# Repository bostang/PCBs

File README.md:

# PCBs
My repository for documenting all PCB Projects I have done

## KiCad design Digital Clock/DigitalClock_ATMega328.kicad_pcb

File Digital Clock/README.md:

# Digital Clock

# Skematik

# Tampilan

## Tampak Atas

## Tampak Bawah

## Bird-view

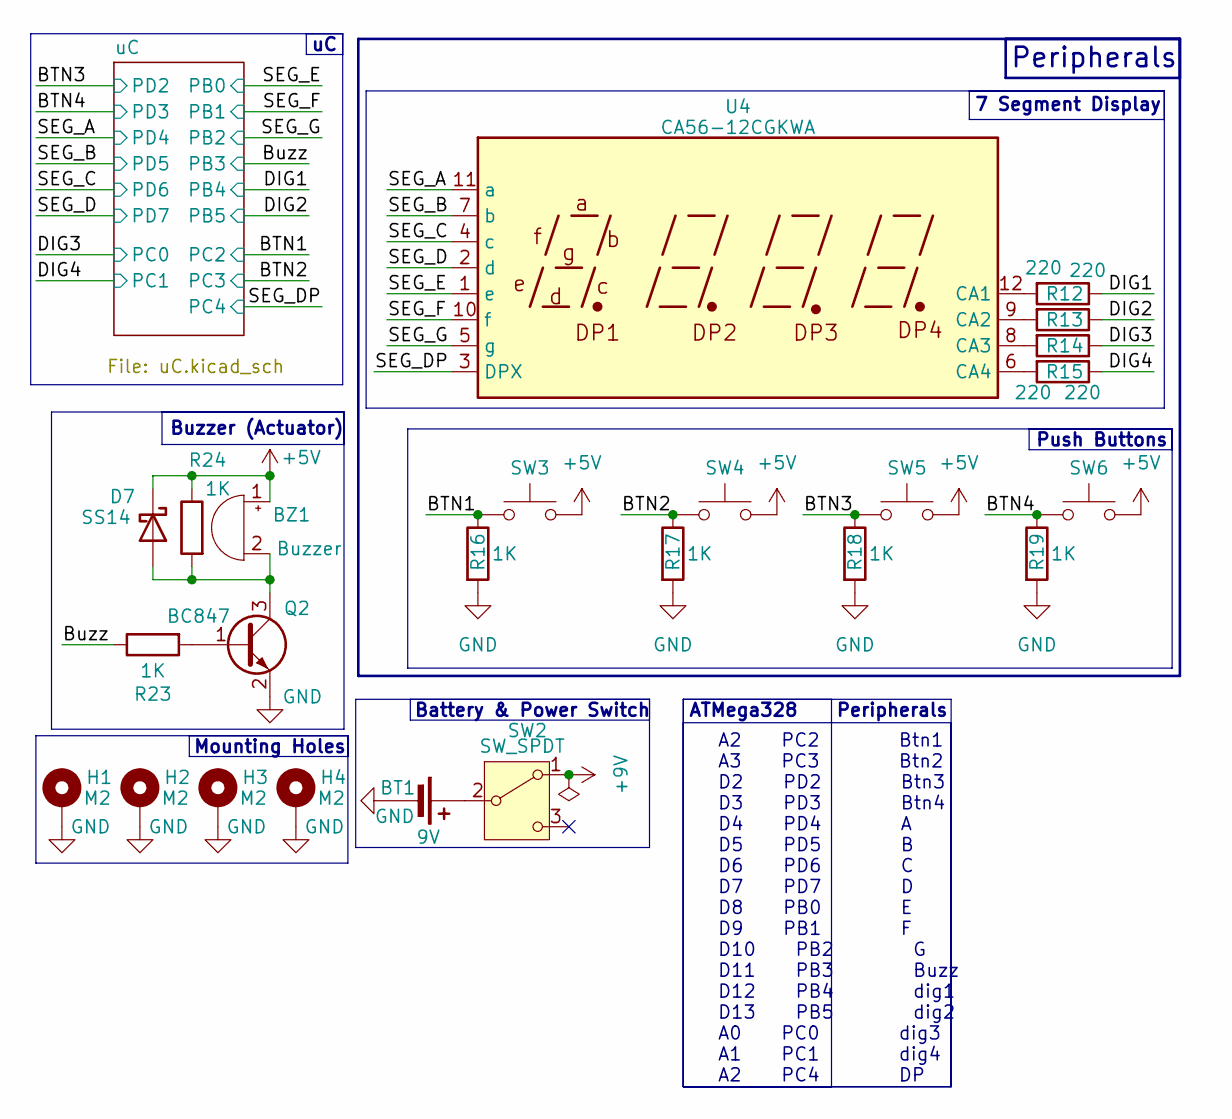
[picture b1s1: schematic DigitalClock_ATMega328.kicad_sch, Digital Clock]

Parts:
BT1: 9V; BatteryHolder_Eagle_12BH611-GR
BZ1: Buzzer; MagneticBuzzer_Kobitone_254-EMB84Q-RO
D7: SS14; D_SMA
H1, H2, H3, H4: M2; MountingHole_2.2mm_M2_Pad_Via
Q2: BC847; SOT-23
R12, R13, R14, R15: 220; R_0805_2012Metric
R16, R17, R18, R19, R23, R24: 1K; R_0805_2012Metric
SW2: SW_SPDT; SW_Slide_SPDT_Angled_CK_OS102011MA1Q
SW3, SW4, SW5, SW6: SW_Push; SW_SPST_PTS645
U4: CA56-12CGKWA

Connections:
+5V: BZ1.1 (+), D7.1 (K), R24.1, SW3.2, SW4.2, SW5.2, SW6.2; also elsewhere on the board
+9V: SW2.1 (A); also elsewhere on the board
/BTN1: R16.1, SW3.1; also elsewhere on the board
/BTN2: R17.1, SW4.1; also elsewhere on the board
/BTN3: R18.1, SW5.1; also elsewhere on the board
/BTN4: R19.1, SW6.1; also elsewhere on the board
/Buzz: R23.1; also elsewhere on the board
/DIG1: R12.1; also elsewhere on the board
/DIG2: R13.1; also elsewhere on the board
/DIG3: R14.1; also elsewhere on the board
/DIG4: R15.1; also elsewhere on the board
/SEG_A: U4.11 (a); also elsewhere on the board
/SEG_B: U4.7 (b); also elsewhere on the board
/SEG_C: U4.4 (c); also elsewhere on the board
/SEG_D: U4.2 (d); also elsewhere on the board
/SEG_DP: U4.3 (DPX); also elsewhere on the board
/SEG_E: U4.1 (e); also elsewhere on the board
/SEG_F: U4.10 (f); also elsewhere on the board
/SEG_G: U4.5 (g); also elsewhere on the board
GND: BT1.2 (-), H1.1, H2.1, H3.1, H4.1, Q2.2 (E), R16.2, R17.2, R18.2, R19.2; also elsewhere on the board
unnamed: BT1.1 (+), SW2.2 (B)
unnamed: BZ1.2 (-), D7.2 (A), Q2.3 (C), R24.2
unnamed: Q2.1 (B), R23.2
unnamed: R12.2, U4.12 (CA1)
unnamed: R13.2, U4.9 (CA2)
unnamed: R14.2, U4.8 (CA3)
unnamed: R15.2, U4.6 (CA4)

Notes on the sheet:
7 Segment Display
Push Buttons
A2 PC2 Btn1 A3 PC3 Btn2 D2 PD2 Btn3 D3 PD3 Btn4 D4 PD4 A D5 PD5 B D6 PD6 C D7 PD7 D D8 PB0 E D9 PB1 F D10 PB2 G D11 PB3 Buzz D12 PB4 dig1 D13 PB5 dig2 A0 PC0 dig3 A1 PC1 dig4 A2 PC4 DP
Buzzer (Actuator)
Mounting Holes
Battery & Power Switch
ATMega328 Peripherals
Peripherals

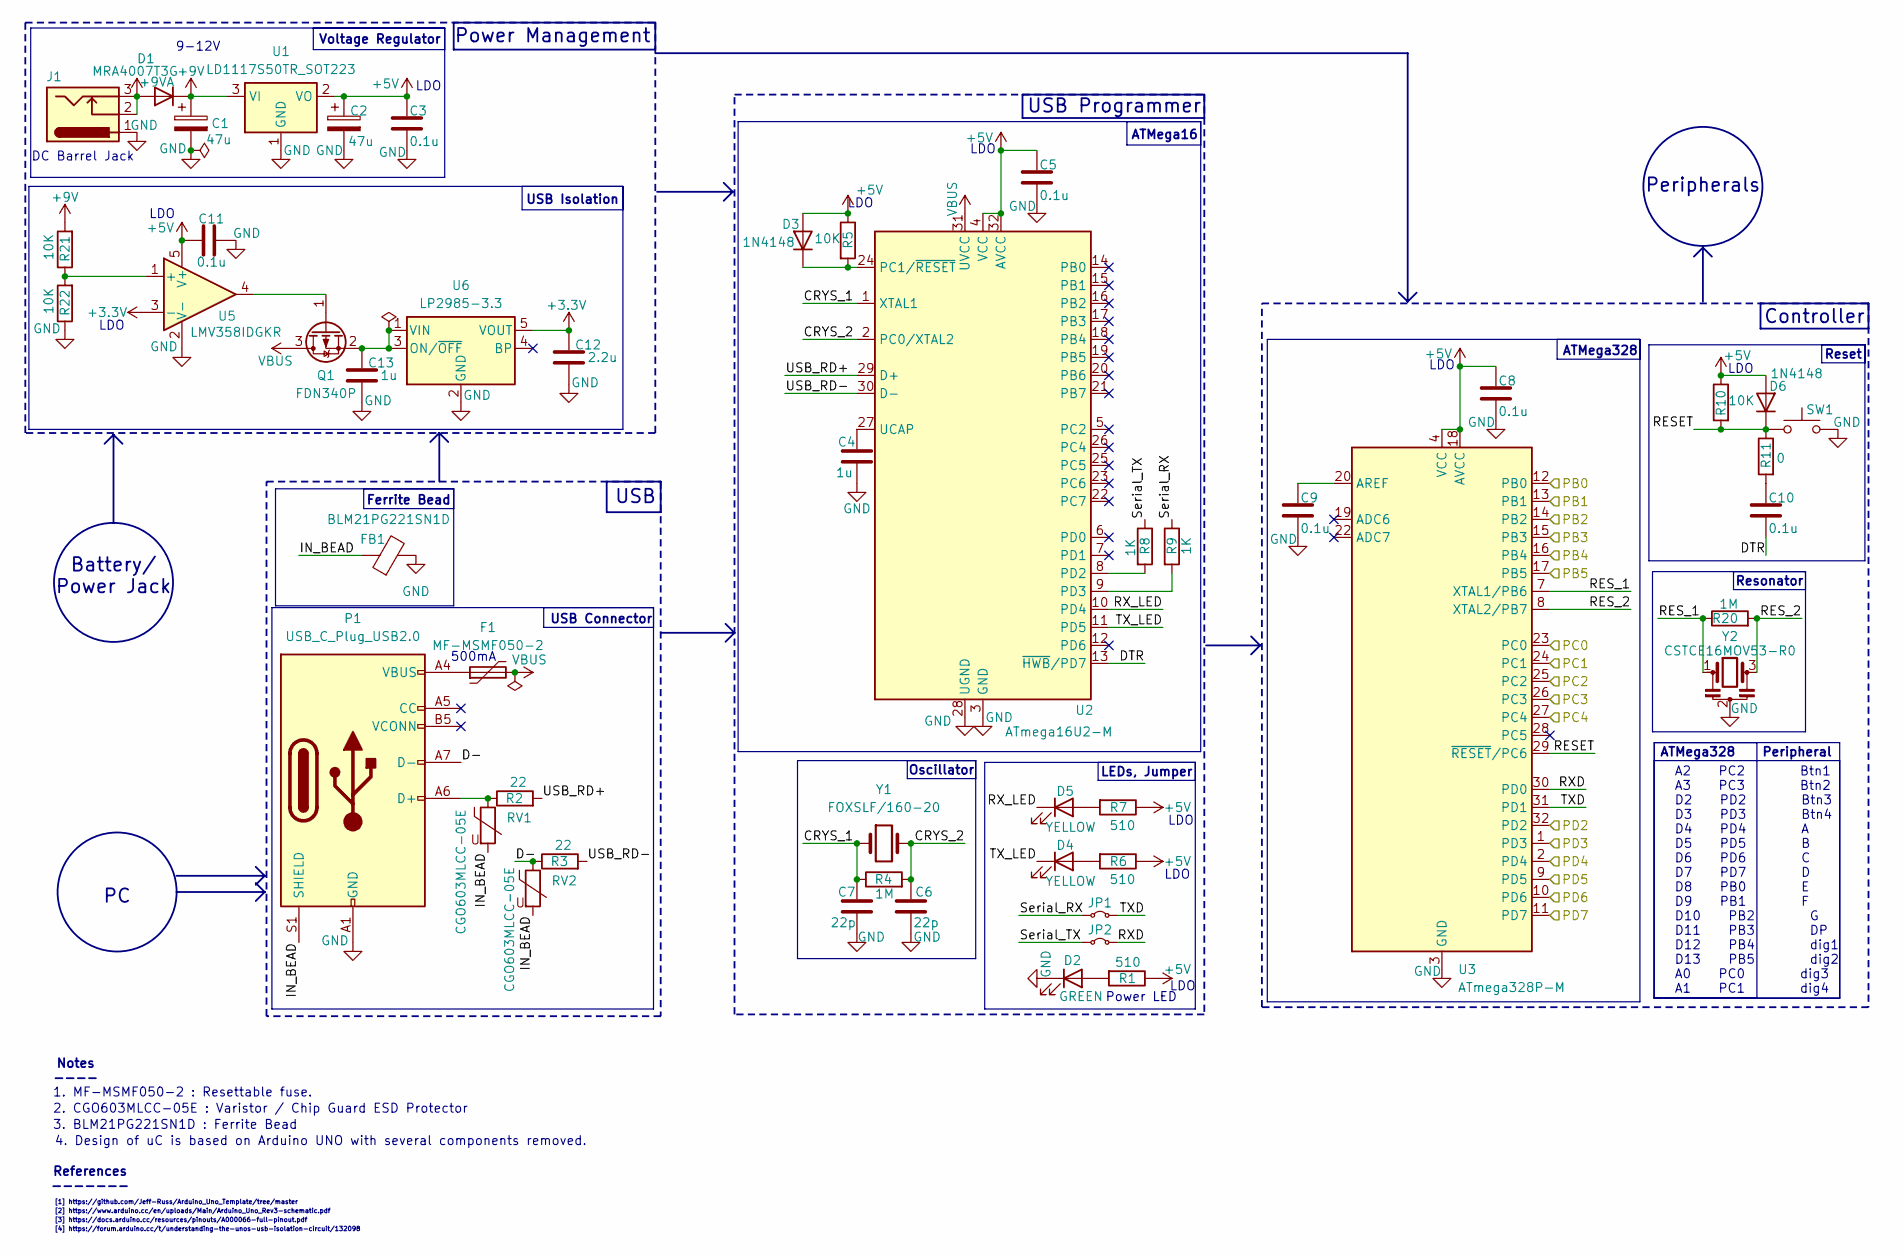
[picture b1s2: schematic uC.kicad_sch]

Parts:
C1, C2: 47u; C_Elec_3x5.4
C3: 0.1u; C_1206_3216Metric
C4: 1u; C_0201_0603Metric
C5, C8, C9, C11: 0.1u; C_0201_0603Metric
C6, C7: 22p; C_0201_0603Metric
C10: 0.1u; C_0805_2012Metric
C12: 2.2u; C_0402_1005Metric
C13: 1u; C_0402_1005Metric
D1: MRA4007T3G; D_SMA
D2: GREEN; LED_0805_2012Metric
D3, D6: 1N4148; D_SOD-323F
D4, D5: YELLOW; LED_0805_2012Metric
F1: MF-MSMF050-2; R_1812_4532Metric
FB1: BLM21PG221SN1D; R_0603_1608Metric
J1: Barrel_Jack_Switch_Pin3Ring; BarrelJack_Horizontal
JP1, JP2: Jumper_2_Small_Bridged; SolderJumper-2_P1.3mm_Bridged_Pad1.0x1.5mm
P1: USB_C_Plug_USB2.0; USB_C_Receptacle_GCT_USB4105-xx-A_16P_TopMnt_Horizontal
Q1: FDN340P; SOT-23
R1, R6, R7: 510; R_0805_2012Metric
R2, R3: 22; R_0603_1608Metric
R4: 1M; R_0805_2012Metric
R5, R21, R22: 10K; R_0201_0603Metric
R8, R9: 1K; R_0201_0603Metric
R10: 10K; R_0805_2012Metric
R11: 0; R_0805_2012Metric
R20: 1M; R_0201_0603Metric
RV1, RV2: CGO603MLCC-05E; R_0603_1608Metric
SW1: SW_Push; SW_SPST_B3U-1000P
U1: LD1117S50TR_SOT223; SOT-223-3_TabPin2
U2: ATmega16U2-M; QFN-32-1EP_5x5mm_P0.5mm_EP3.3x3.3mm
U3: ATmega328P-M; QFN-32-1EP_5x5mm_P0.5mm_EP3.3x3.3mm
U5: LMV358IDGKR; VSSOP-8_2.3x2mm_P0.5mm
U6: LP2985-3.3; SOT-23-5
Y1: FOXSLF/160-20; Crystal_HC49-4H_Vertical
Y2: CSTCE16MOV53-R0; Resonator_SMD_Murata_CSTxExxV-3Pin_3.0x1.1mm

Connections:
+3.3V: C12.1, U5.3 (-), U6.5 (VOUT)
+5V: C2.1, C3.1, C5.1, C8.1, C11.1, D3.2 (A), D6.2 (A), R1.1, R5.1, R6.1, R7.1, R10.1, U1.2 (VO), U2.4 (VCC), U2.32 (AVCC), U3.4 (VCC), U3.6 (VCC), U3.18 (AVCC), U5.5 (V+); also elsewhere on the board
+9V: C1.1, D1.1 (K), R21.2, U1.3 (VI); also elsewhere on the board
+9VA: D1.2 (A), J1.2, J1.3
/BTN1: U3.25 (PC2); also elsewhere on the board
/BTN2: U3.26 (PC3); also elsewhere on the board
/BTN3: U3.32 (PD2); also elsewhere on the board
/BTN4: U3.1 (PD3); also elsewhere on the board
/Buzz: U3.15 (PB3); also elsewhere on the board
/DIG1: U3.16 (PB4); also elsewhere on the board
/DIG2: U3.17 (PB5); also elsewhere on the board
/DIG3: U3.23 (PC0); also elsewhere on the board
/DIG4: U3.24 (PC1); also elsewhere on the board
/SEG_A: U3.2 (PD4); also elsewhere on the board
/SEG_B: U3.9 (PD5); also elsewhere on the board
/SEG_C: U3.10 (PD6); also elsewhere on the board
/SEG_D: U3.11 (PD7); also elsewhere on the board
/SEG_DP: U3.27 (PC4); also elsewhere on the board
/SEG_E: U3.12 (PB0); also elsewhere on the board
/SEG_F: U3.13 (PB1); also elsewhere on the board
/SEG_G: U3.14 (PB2); also elsewhere on the board
/uC/CRYS_1: C7.1, R4.1, U2.1 (XTAL1), Y1.1
/uC/CRYS_2: C6.1, R4.2, U2.2 (PC0/XTAL2), Y1.2
/uC/D-: P1.A7 (D-), R3.1, RV2.1
/uC/DTR: C10.2, U2.13 (~HWB/PD7)
/uC/IN_BEAD: FB1.1, P1.S1 (SHIELD), RV1.2, RV2.2
/uC/RESET: D6.1 (K), R10.2, R11.1, SW1.1, U3.29 (~RESET/PC6)
/uC/RES_1: R20.1, U3.7 (XTAL1/PB6), Y2.1
/uC/RES_2: R20.2, U3.8 (XTAL2/PB7), Y2.3
/uC/RXD: JP2.2 (B), U3.30 (PD0)
/uC/RX_LED: D5.1 (K), U2.10 (PD4)
/uC/Serial_RX: JP1.1 (A), R9.1
/uC/Serial_TX: JP2.1 (A), R8.1
/uC/TXD: JP1.2 (B), U3.31 (PD1)
/uC/TX_LED: D4.1 (K), U2.11 (PD5)
/uC/USB_RD+: R2.2, U2.29 (D+)
/uC/USB_RD-: R3.2, U2.30 (D-)
GND: C1.2, C2.2, C3.2, C4.2, C5.2, C6.2, C7.2, C8.2, C9.2, C11.2, C12.2, C13.2, D2.1 (K), FB1.2, J1.1, P1.A1 (GND), P1.A12 (GND), P1.B1 (GND), P1.B12 (GND), R22.1, SW1.2, U1.1 (GND), U2.3 (GND), U2.28 (UGND), U2.33 (GND), U3.3 (GND), U3.5 (GND), U3.21 (GND), U3.33 (GND), U5.2 (V-), U6.2 (GND), Y2.2; also elsewhere on the board
unnamed: C10.1, R11.2
unnamed: D2.2 (A), R1.2
unnamed: D3.1 (K), R5.2, U2.24 (PC1/~RESET)
unnamed: D4.2 (A), R6.2
unnamed: D5.2 (A), R7.2
unnamed: F1.1, P1.A4 (VBUS), P1.A9 (VBUS), P1.B4 (VBUS), P1.B9 (VBUS)
unnamed: P1.A6 (D+), R2.1, RV1.1
unnamed: Q1.1 (G), U5.4
unnamed: C13.1, Q1.2 (S), U6.1 (VIN), U6.3 (ON/~OFF)
unnamed: R8.2, U2.8 (PD2)
unnamed: R9.2, U2.9 (PD3)
unnamed: C4.1, U2.27 (UCAP)
unnamed: C9.1, U3.20 (AREF)
unnamed: R21.1, R22.2, U5.1 (+)
VBUS: F1.2, Q1.3 (D), U2.31 (UVCC)

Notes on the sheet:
LDO
Power Management
References -------
Resonator
Oscillator
[2] https://www.arduino.cc/en/uploads/Main/Arduino_Uno_Rev3-schematic.pdf
1. MF-MSMF050-2 : Resettable fuse.
ATMega328 Peripheral
[4] https://forum.arduino.cc/t/understanding-the-unos-usb-isolation-circuit/132098
ATMega16
ATMega328
Controller
DC Barrel Jack
Notes ----
4. Design of uC is based on Arduino UNO with several components removed.
[3] https://docs.arduino.cc/resources/pinouts/A000066-full-pinout.pdf
3. BLM21PG221SN1D : Ferrite Bead
[1] https://github.com/Jeff-Russ/Arduino_Uno_Template/tree/master
500mA
USB
USB Connector
USB Programmer
A2 PC2 Btn1 A3 PC3 Btn2 D2 PD2 Btn3 D3 PD3 Btn4 D4 PD4 A D5 PD5 B D6 PD6 C D7 PD7 D D8 PB0 E D9 PB1 F D10 PB2 G D11 PB3 DP D12 PB4 dig1 D13 PB5 dig2 A0 PC0 dig3 A1 PC1 dig4
2. CGO603MLCC-05E : Varistor / Chip Guard ESD Protector
Battery/ Power Jack
LEDs, Jumper
Ferrite Bead
USB Isolation
Voltage Regulator
Power LED
Peripherals
Reset
9-12V

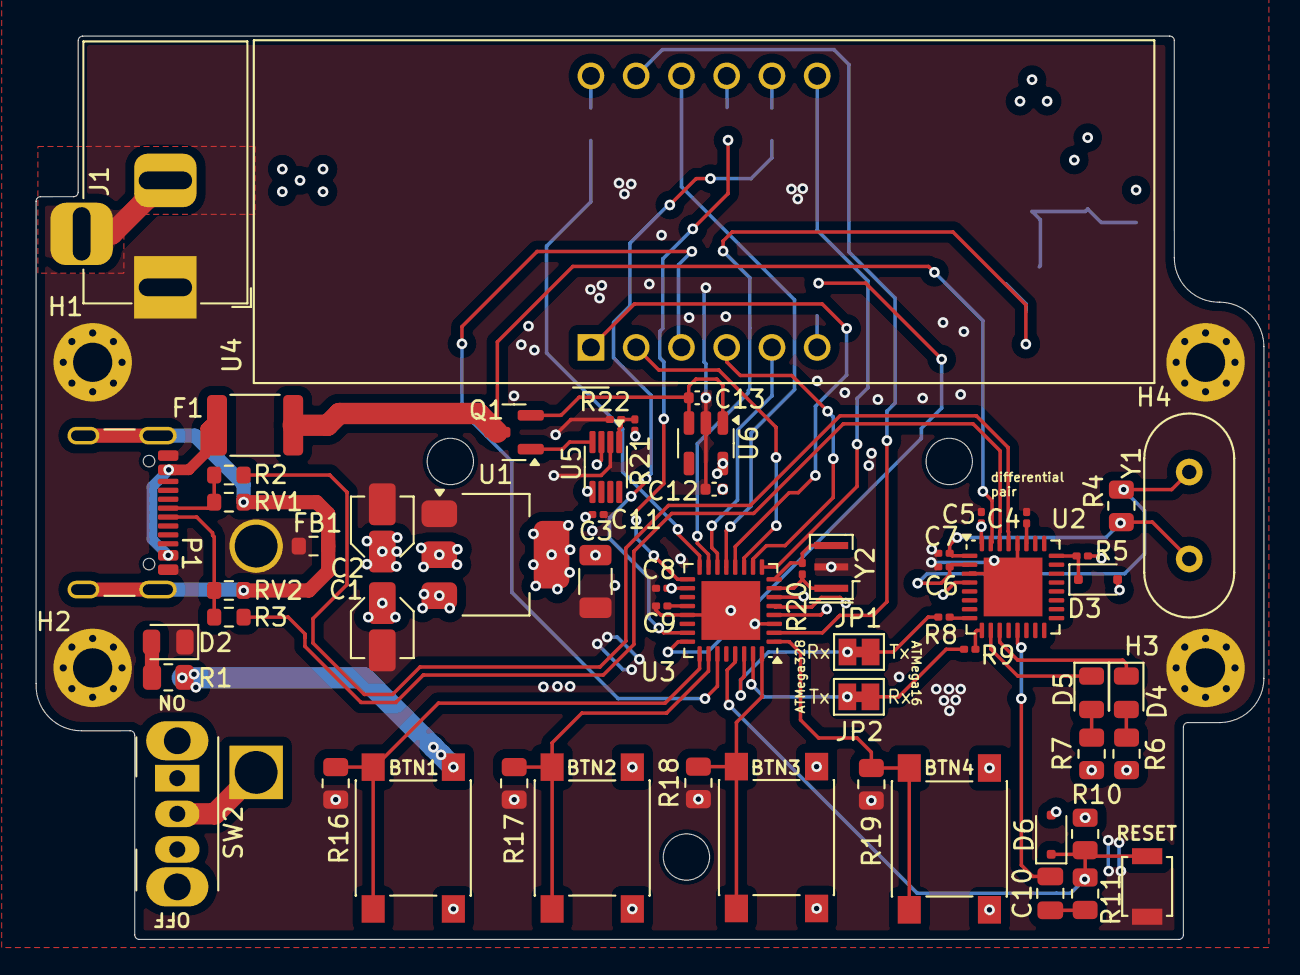
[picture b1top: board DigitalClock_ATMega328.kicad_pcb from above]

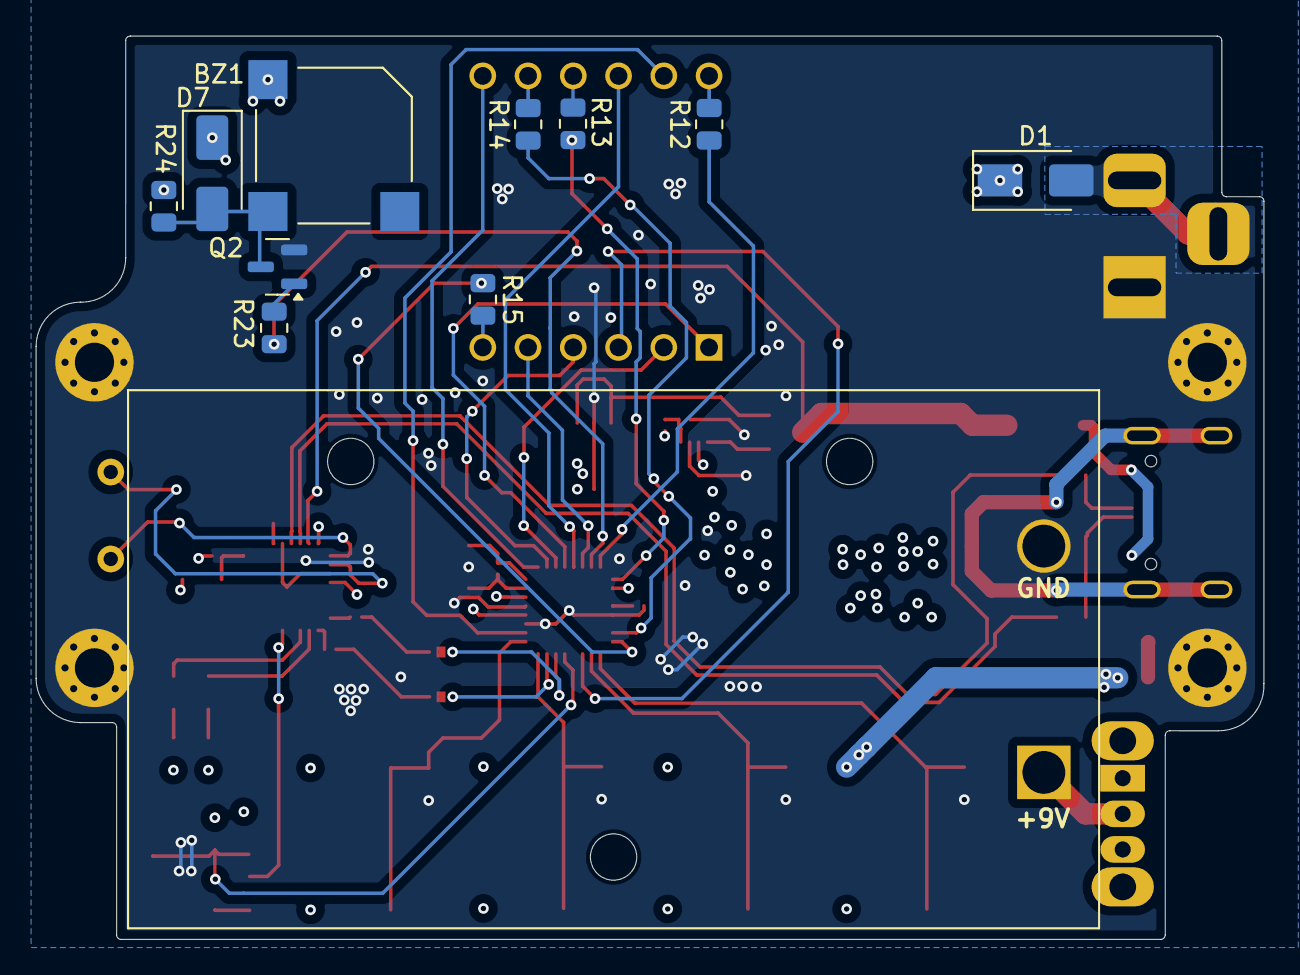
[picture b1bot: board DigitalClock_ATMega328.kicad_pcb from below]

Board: 4 copper layers, 68.9 x 50.7 mm, 74 parts (11 on the bottom side), 60 nets.

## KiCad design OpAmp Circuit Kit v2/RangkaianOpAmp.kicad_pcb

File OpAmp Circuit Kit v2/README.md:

# Op Amp Circuits Kit

Kit Praktikum EL2101 Praktikum Rangkaian Elektrik Modul 3. (v2)

# Skematik

# Tampilan

## Tampak Atas

## Tampak Bawah

## Bird-view

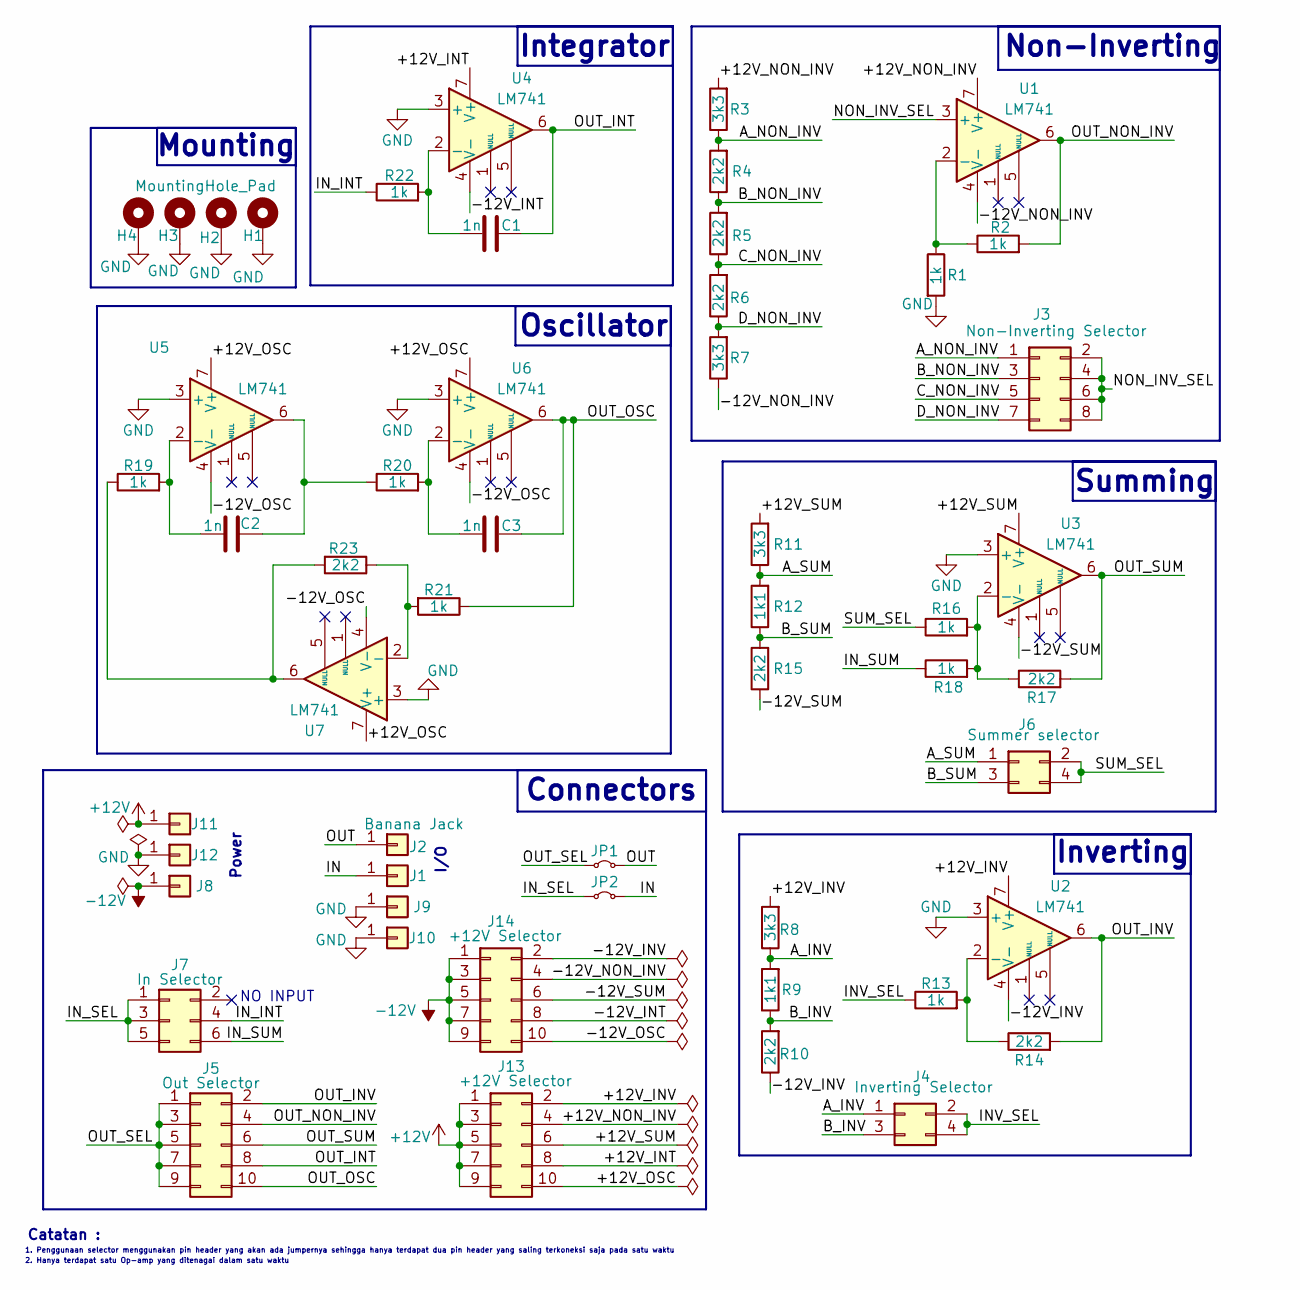
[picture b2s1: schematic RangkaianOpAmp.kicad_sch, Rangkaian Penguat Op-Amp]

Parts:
C1, C2, C3: 1n; C_0805_2012Metric
H1, H2, H3, H4: MountingHole_Pad; MountingHole_3.2mm_M3_Pad_Via
J1, J2, J8, J9, J10, J11, J12: Banana Jack; Banana_Jack_1Pin
J3: Non-Inverting Selector; PinHeader_2x04_P2.54mm_Vertical
J4: Inverting Selector; PinHeader_2x02_P2.54mm_Vertical
J5: Out Selector; PinHeader_2x05_P2.54mm_Vertical
J6: Summer selector; PinHeader_2x02_P2.54mm_Vertical
J7: In Selector; PinHeader_2x03_P2.54mm_Vertical
J13, J14: +12V Selector; PinHeader_2x05_P2.54mm_Vertical
JP1, JP2: Jumper_2_Small_Bridged; SolderJumper-2_P1.3mm_Bridged2Bar_RoundedPad1.0x1.5mm
R1, R2, R13, R16, R18, R19, R20, R21, R22: 1k; R_0805_2012Metric
R3, R7, R8, R11: 3k3; R_0805_2012Metric
R4, R5, R6, R10, R14, R15, R17, R23: 2k2; R_0805_2012Metric
R9, R12: 1k1; R_0805_2012Metric
U1, U2, U3, U4, U5, U6, U7: LM741; SOIC-8_3.9x4.9mm_P1.27mm

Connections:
+12V: J11.1, J13.1, J13.3, J13.5, J13.7, J13.9
-12V: J8.1, J14.1, J14.3, J14.5, J14.7, J14.9
/+12V_INT: J13.8, U4.7 (V+)
/+12V_INV: J13.2, R8.2, U2.7 (V+)
/+12V_NON_INV: J13.4, R3.2, U1.7 (V+)
/+12V_OSC: J13.10, U5.7 (V+), U6.7 (V+), U7.7 (V+)
/+12V_SUM: J13.6, R11.2, U3.7 (V+)
/-12V_INT: J14.8, U4.4 (V-)
/-12V_INV: J14.2, R10.1, U2.4 (V-)
/-12V_NON_INV: J14.4, R7.1, U1.4 (V-)
/-12V_OSC: J14.10, U5.4 (V-), U6.4 (V-), U7.4 (V-)
/-12V_SUM: J14.6, R15.1, U3.4 (V-)
/A_INV: J4.1, R8.1, R9.2
/A_NON_INV: J3.1, R3.1, R4.2
/A_SUM: J6.1, R11.1, R12.2
/B_INV: J4.3, R9.1, R10.2
/B_NON_INV: J3.3, R4.1, R5.2
/B_SUM: J6.3, R12.1, R15.2
/C_NON_INV: J3.5, R5.1, R6.2
/D_NON_INV: J3.7, R6.1, R7.2
/IN: J1.1, JP2.2 (B)
/INV_SEL: J4.2, J4.4, R13.1
/IN_INT: J7.4, R22.1
/IN_SEL: J7.1, J7.3, J7.5, JP2.1 (A)
/IN_SUM: J7.6, R18.1
/NON_INV_SEL: J3.2, J3.4, J3.6, J3.8, U1.3 (+)
/OUT: J2.1, JP1.2 (B)
/OUT_INT: C1.2, J5.8, U4.6
/OUT_INV: J5.2, R14.2, U2.6
/OUT_NON_INV: J5.4, R2.2, U1.6
/OUT_OSC: C3.2, J5.10, R21.1, U6.6
/OUT_SEL: J5.1, J5.3, J5.5, J5.7, J5.9, JP1.1 (A)
/OUT_SUM: J5.6, R17.2, U3.6
/SUM_SEL: J6.2, J6.4, R16.1
GND: H1.1, H2.1, H3.1, H4.1, J9.1, J10.1, J12.1, R1.2, U2.3 (+), U3.3 (+), U4.3 (+), U5.3 (+), U6.3 (+), U7.3 (+)
unnamed: C2.2, R20.1, U5.6
unnamed: R19.1, R23.2, U7.6
unnamed: R1.1, R2.1, U1.2 (-)
unnamed: R13.2, R14.1, U2.2 (-)
unnamed: R16.2, R17.1, R18.2, U3.2 (-)
unnamed: C1.1, R22.2, U4.2 (-)
unnamed: C2.1, R19.2, U5.2 (-)
unnamed: C3.1, R20.2, U6.2 (-)
unnamed: R21.2, R23.1, U7.2 (-)

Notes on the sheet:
Inverting
Summing
Connectors
Mounting
Catatan :
1. Penggunaan selector menggunakan pin header yang akan ada jumpernya sehingga hanya terdapat dua pin header yang saling terkoneksi saja pada satu waktu
2. Hanya terdapat satu Op-amp yang ditenagai dalam satu waktu
Power
Non-Inverting
NO INPUT
Integrator
Oscillator
I/O

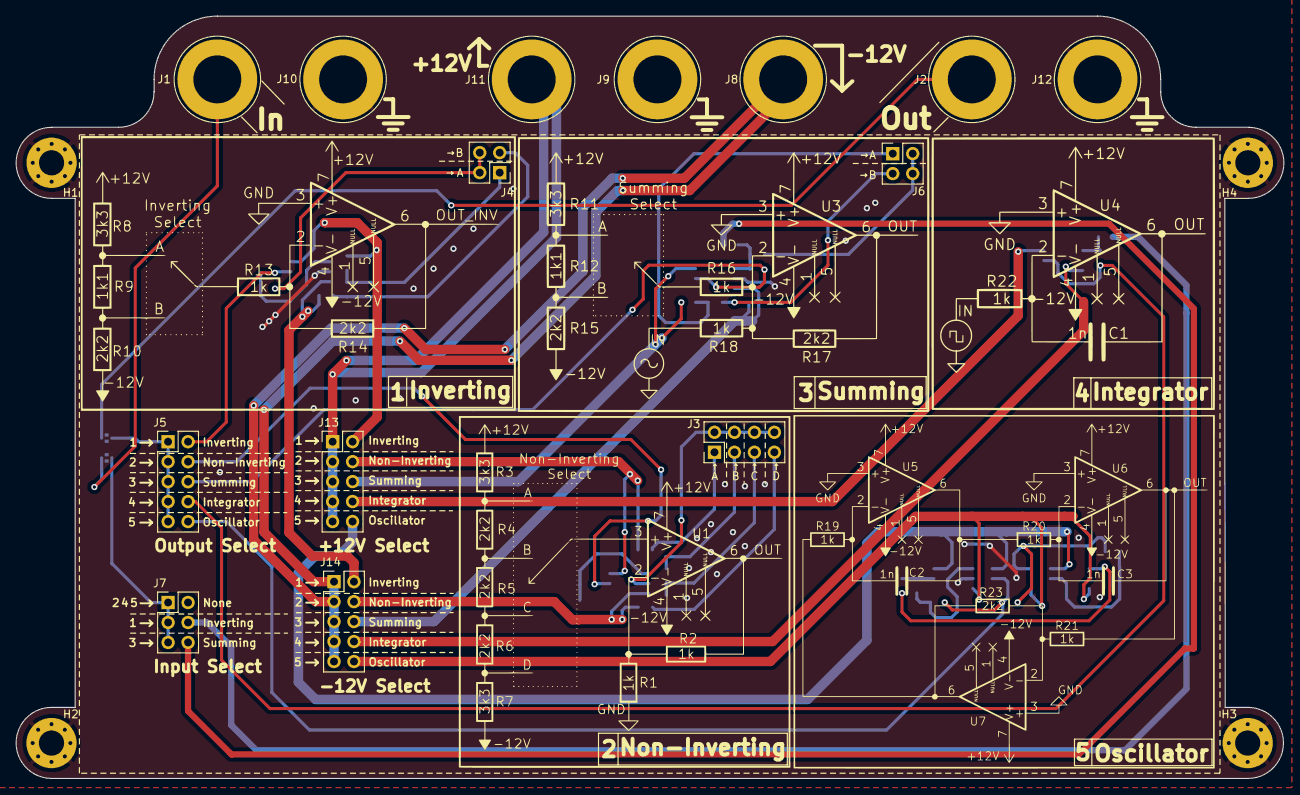
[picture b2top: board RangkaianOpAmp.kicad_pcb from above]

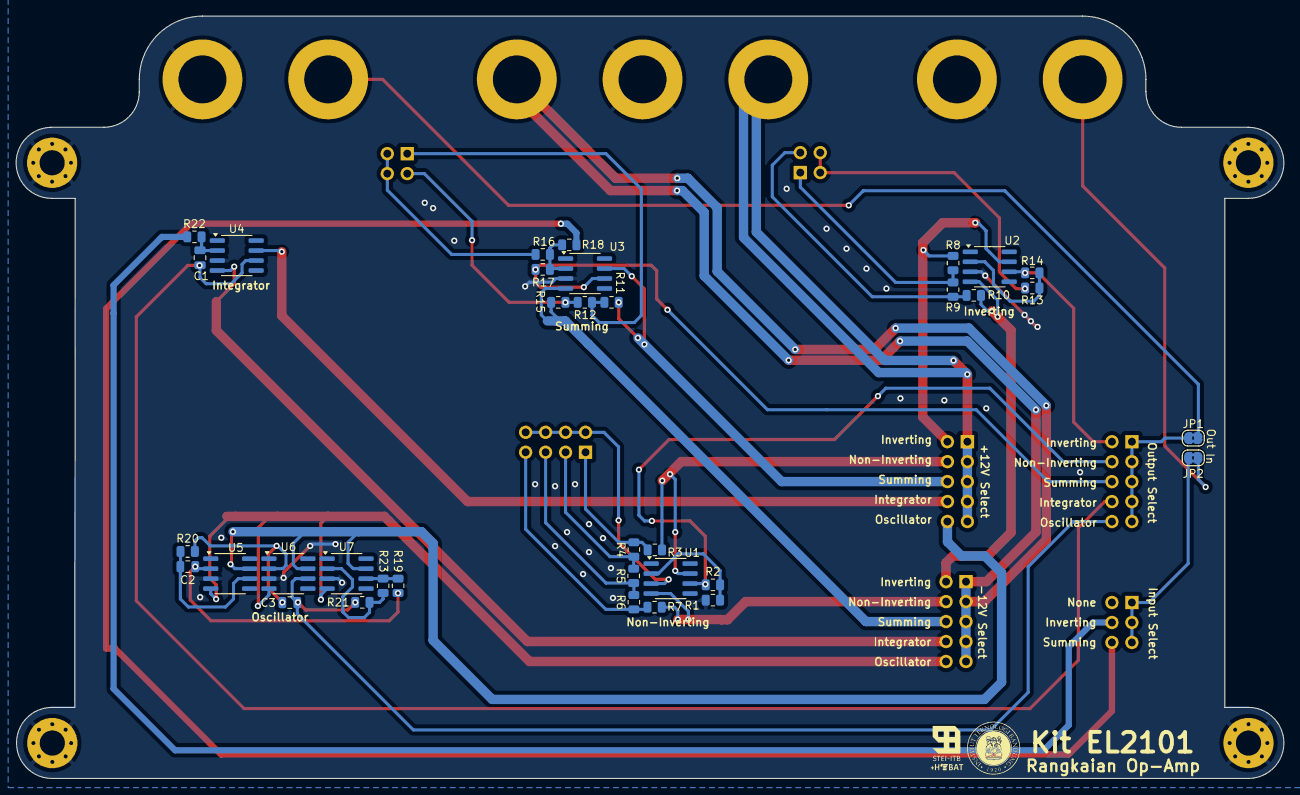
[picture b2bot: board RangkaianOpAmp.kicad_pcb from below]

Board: 2 copper layers, 161.3 x 97.0 mm, 53 parts (35 on the bottom side), 44 nets.

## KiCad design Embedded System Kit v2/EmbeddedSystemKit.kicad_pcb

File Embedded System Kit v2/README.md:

# Embedded System Kit (v2)

# Skematik

# Tampilan

## Tampak Atas

## Tampak Bawah

## Bird-view

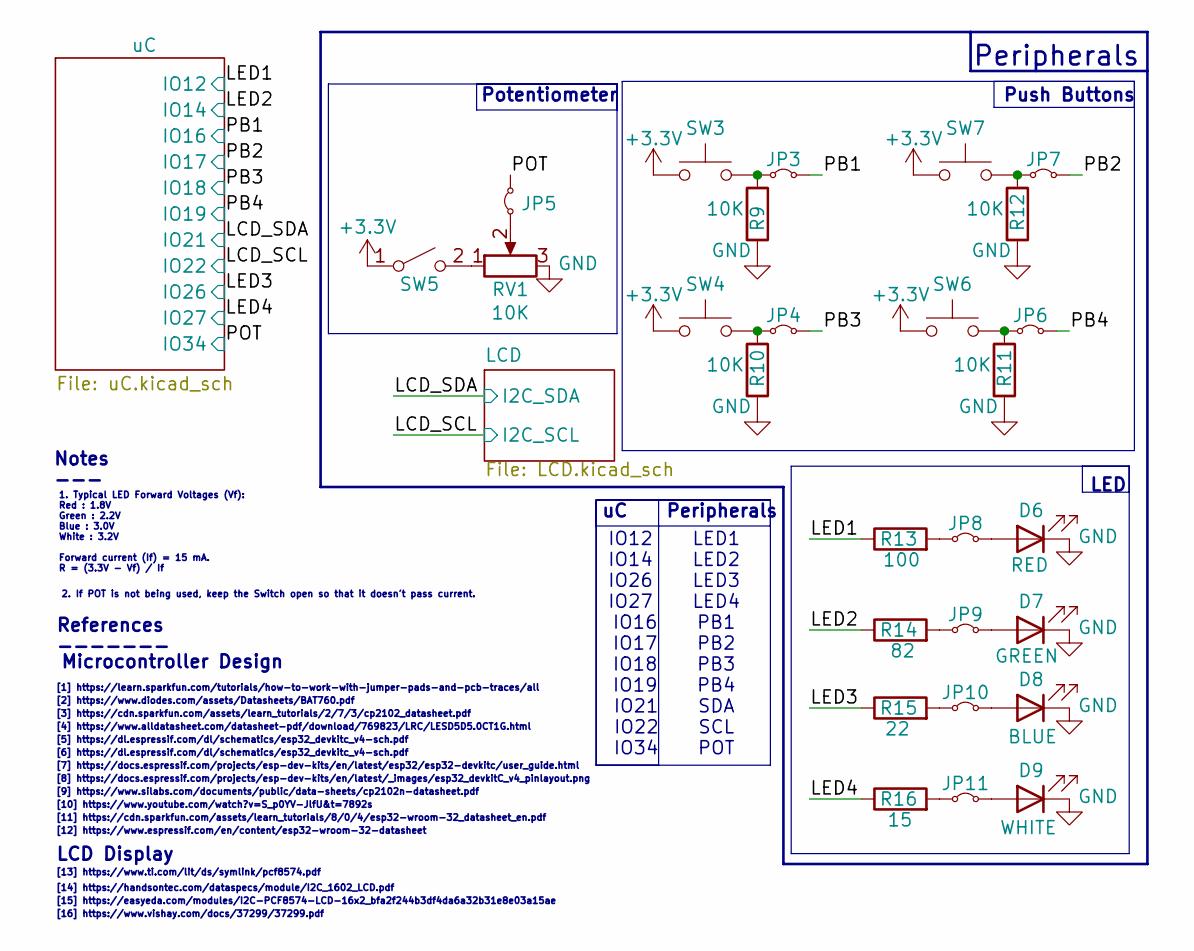
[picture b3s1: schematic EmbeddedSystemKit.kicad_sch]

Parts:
D6: RED; LED_0805_2012Metric
D7: GREEN; LED_0805_2012Metric
D8: BLUE; LED_0805_2012Metric
D9: WHITE; LED_0805_2012Metric
JP3, JP4, JP5, JP6, JP7, JP8, JP9, JP10, JP11: Jumper_2_Small_Bridged; R_0805_2012Metric
R9, R10, R11, R12: 10K; R_0805_2012Metric
R13: 100; R_0805_2012Metric
R14: 82; R_0805_2012Metric
R15: 22; R_0805_2012Metric
R16: 15; R_0805_2012Metric
RV1: 10K; Potentiometer_Bourns_PTV09A-1_Single_Vertical
SW3, SW4, SW6, SW7: SW_Push; SW_PUSH_6mm_H8mm
SW5: SW_SPST; SW_DIP_SPSTx01_Slide_6.7x4.1mm_W7.62mm_P2.54mm_LowProfile

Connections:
+3.3V: SW3.1, SW4.1, SW5.1 (A), SW6.1, SW7.1; also elsewhere on the board
/LED1: R13.1; also elsewhere on the board
/LED2: R14.1; also elsewhere on the board
/LED3: R15.1; also elsewhere on the board
/LED4: R16.1; also elsewhere on the board
/PB1: JP3.2 (B); also elsewhere on the board
/PB2: JP7.2 (B); also elsewhere on the board
/PB3: JP4.2 (B); also elsewhere on the board
/PB4: JP6.2 (B); also elsewhere on the board
/POT: JP5.2 (B); also elsewhere on the board
GND: D6.1 (K), D7.1 (K), D8.1 (K), D9.1 (K), R9.2, R10.2, R11.2, R12.2, RV1.3; also elsewhere on the board
unnamed: D6.2 (A), JP8.2 (B)
unnamed: D7.2 (A), JP9.2 (B)
unnamed: D8.2 (A), JP10.2 (B)
unnamed: D9.2 (A), JP11.2 (B)
unnamed: JP3.1 (A), R9.1, SW3.2
unnamed: JP4.1 (A), R10.1, SW4.2
unnamed: JP5.1 (A), RV1.2
unnamed: JP6.1 (A), R11.1, SW6.2
unnamed: JP7.1 (A), R12.1, SW7.2
unnamed: JP8.1 (A), R13.2
unnamed: JP9.1 (A), R14.2
unnamed: JP10.1 (A), R15.2
unnamed: JP11.1 (A), R16.2
unnamed: RV1.1, SW5.2 (B)

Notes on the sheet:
[5] https://dl.espressif.com/dl/schematics/esp32_devkitc_v4-sch.pdf
[8] https://docs.espressif.com/projects/esp-dev-kits/en/latest/_images/esp32_devkitC_v4_pinlayout.png
[9] https://www.silabs.com/documents/public/data-sheets/cp2102n-datasheet.pdf
Peripherals
[14] https://handsontec.com/dataspecs/module/I2C_1602_LCD.pdf
Push Buttons
[11] https://cdn.sparkfun.com/assets/learn_tutorials/8/0/4/esp32-wroom-32_datasheet_en.pdf
Notes ---
[13] https://www.ti.com/lit/ds/symlink/pcf8574.pdf
[6] https://dl.espressif.com/dl/schematics/esp32_devkitc_v4-sch.pdf
[10] https://www.youtube.com/watch?v=S_p0YV-JlfU&t=7892s
LCD Display
[7] https://docs.espressif.com/projects/esp-dev-kits/en/latest/esp32/esp32-devkitc/user_guide.html
[3] https://cdn.sparkfun.com/assets/learn_tutorials/2/7/3/cp2102_datasheet.pdf
Microcontroller Design
[4] https://www.alldatasheet.com/datasheet-pdf/download/769823/LRC/LESD5D5.0CT1G.html
LED
1. Typical LED Forward Voltages (Vf): Red : 1.8V Green : 2.2V Blue : 3.0V White : 3.2V Forward current (If) = 15 mA. R = (3.3V - Vf) / If
[2] https://www.diodes.com/assets/Datasheets/BAT760.pdf
[1] https://learn.sparkfun.com/tutorials/how-to-work-with-jumper-pads-and-pcb-traces/all
[12] https://www.espressif.com/en/content/esp32-wroom-32-datasheet
IO12 LED1 IO14 LED2 IO26 LED3 IO27 LED4 IO16 PB1 IO17 PB2 IO18 PB3 IO19 PB4 IO21 SDA IO22 SCL IO34 POT
uC Peripherals
2. If POT is not being used, keep the Switch open so that it doesn't pass current.
References -------
Potentiometer
[16] https://www.vishay.com/docs/37299/37299.pdf
[15] https://easyeda.com/modules/I2C-PCF8574-LCD-16x2_bfa2f244b3df4da6a32b31e8e03a15ae

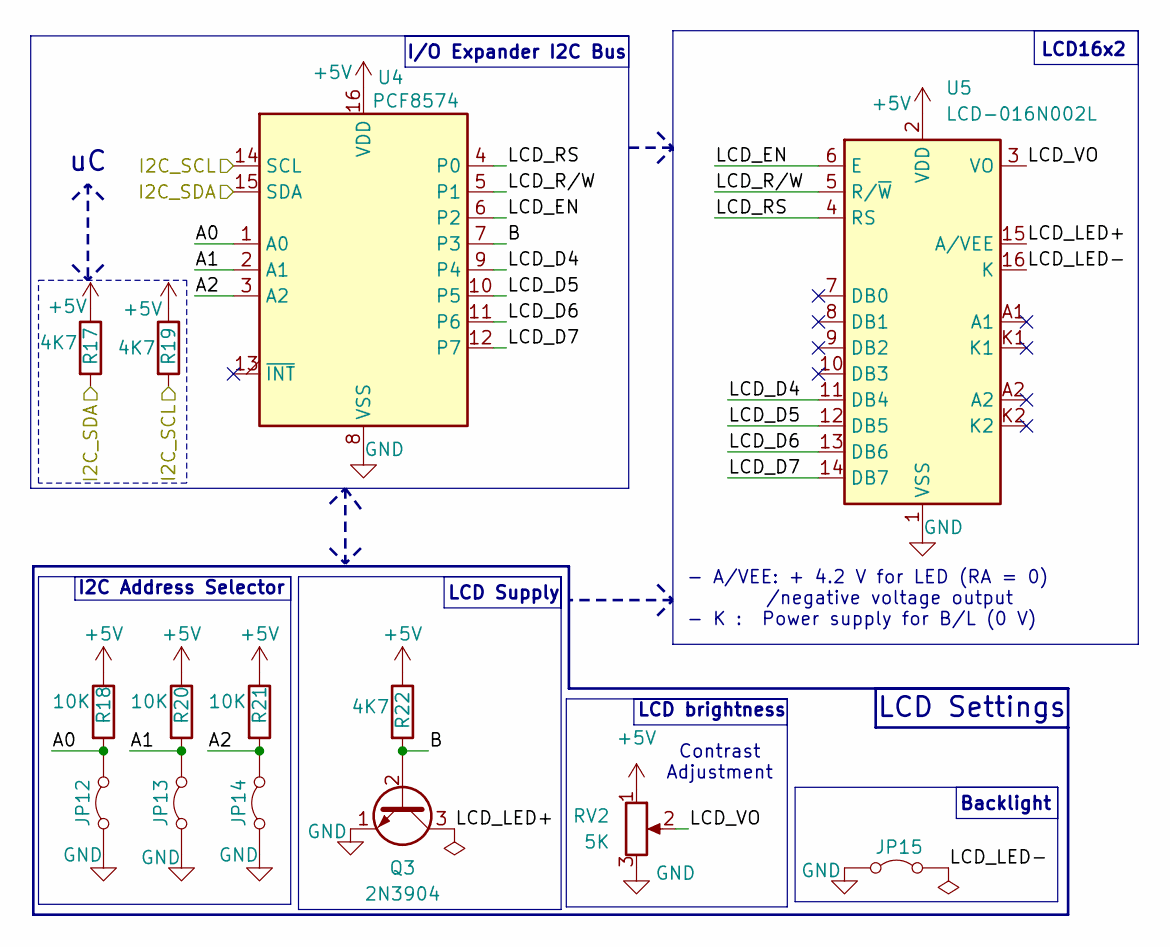
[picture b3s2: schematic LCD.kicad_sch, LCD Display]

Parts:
JP12, JP13, JP14: Jumper_2_Bridged; SolderJumper-2_P1.3mm_Open_Pad1.0x1.5mm
JP15: Jumper_2_Bridged; PinHeader_1x02_P2.54mm_Vertical
Q3: 2N3904; SOT-23
R17, R19, R22: 4K7; R_0805_2012Metric
R18, R20, R21: 10K; R_0805_2012Metric
RV2: 5K; Potentiometer_Bourns_3314G_Vertical
U4: PCF8574; SOIC-16W_7.5x10.3mm_P1.27mm
U5: LCD-016N002L

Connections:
+5V: R17.1, R18.1, R19.1, R20.1, R21.1, R22.1, RV2.1, U4.16 (VDD), U5.2 (VDD); also elsewhere on the board
/LCD/A0: JP12.2 (B), R18.2, U4.1 (A0)
/LCD/A1: JP13.2 (B), R20.2, U4.2 (A1)
/LCD/A2: JP14.2 (B), R21.2, U4.3 (A2)
/LCD/B: Q3.2 (B), R22.2, U4.7 (P3)
/LCD/LCD_D4: U4.9 (P4), U5.11 (DB4)
/LCD/LCD_D5: U4.10 (P5), U5.12 (DB5)
/LCD/LCD_D6: U4.11 (P6), U5.13 (DB6)
/LCD/LCD_D7: U4.12 (P7), U5.14 (DB7)
/LCD/LCD_EN: U4.6 (P2), U5.6 (E)
/LCD/LCD_LED+: Q3.3 (C), U5.15 (A/VEE)
/LCD/LCD_LED-: JP15.2 (B), U5.16 (K)
/LCD/LCD_RS: U4.4 (P0), U5.4 (RS)
/LCD/LCD_R/W: U4.5 (P1), U5.5 (R/~W)
/LCD/LCD_VO: RV2.2, U5.3 (VO)
/LCD_SCL: R19.2, U4.14 (SCL); also elsewhere on the board
/LCD_SDA: R17.2, U4.15 (SDA); also elsewhere on the board
GND: JP12.1 (A), JP13.1 (A), JP14.1 (A), JP15.1 (A), Q3.1 (E), RV2.3, U4.8 (VSS), U5.1 (VSS); also elsewhere on the board

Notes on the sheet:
- A/VEE: + 4.2 V for LED (RA = 0) /negative voltage output - K : Power supply for B/L (0 V)
LCD16x2
LCD Supply
Backlight
Contrast Adjustment
I/O Expander I2C Bus
LCD brightness
I2C Address Selector
LCD Settings
